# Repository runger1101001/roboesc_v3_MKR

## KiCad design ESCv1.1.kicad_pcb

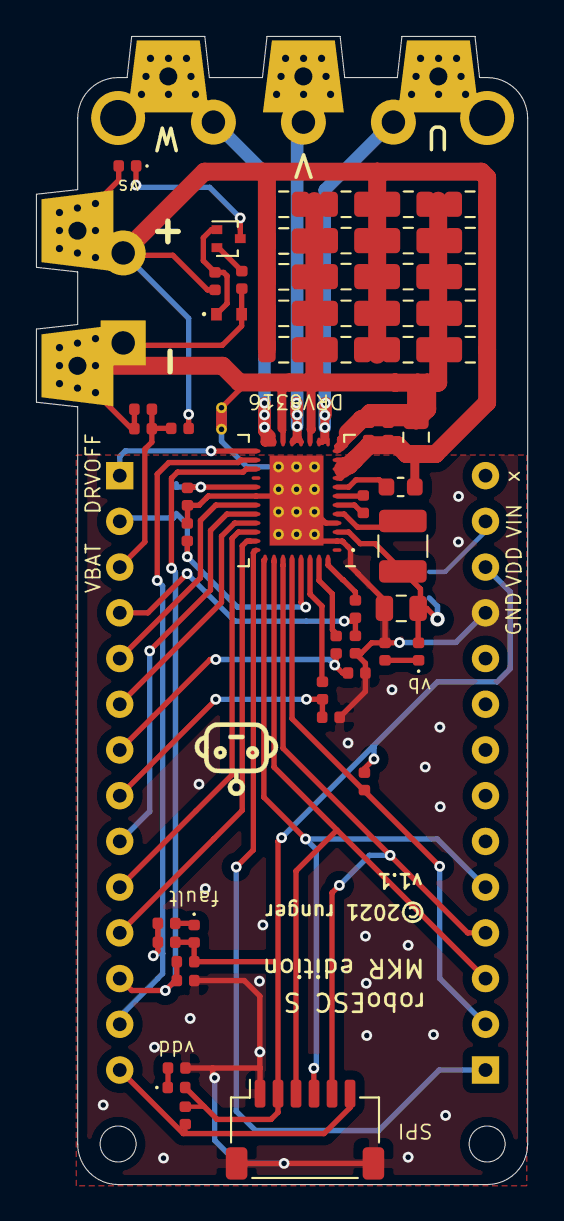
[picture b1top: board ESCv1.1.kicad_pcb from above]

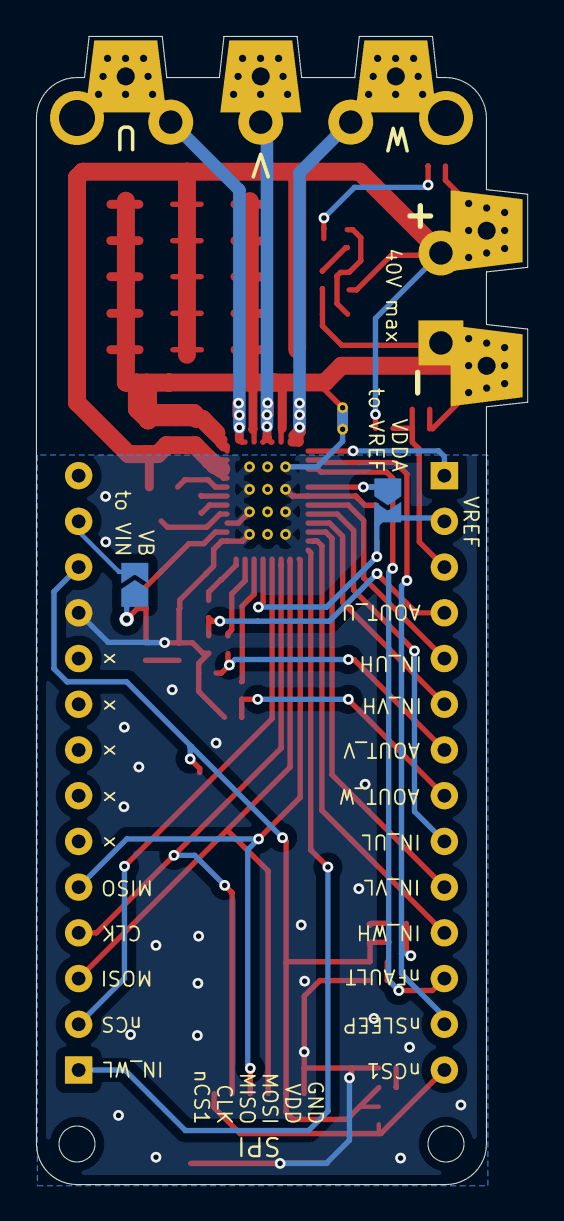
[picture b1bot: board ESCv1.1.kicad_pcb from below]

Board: 2 copper layers, 27.3 x 63.8 mm, 64 parts (3 on the bottom side), 42 nets.

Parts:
C1: 1uF 16V 10%; C_0402_1005Metric
C2: 1nF 16V; C_0402_1005Metric
C3: 22uF 16V; C_0805_2012Metric
C5: 1uF 16V X7R; C_0603_1608Metric
C6: 47nF 50V X7R; C_0402_1005Metric
C7, C8, C9, C11: 100nF 50V 5%; C_0402_1005Metric
C10, C15, C16, C17, C18, C19, C20, C21, C22, C23, C24, C25, C26, C27, C28, C29, C30, C31, C32, C33, C34: 10uF 50V; C_0805_2012Metric
C12, C13, C14: 22pF 50V 1%; C_0402_1005Metric
D1, D2, D3: green; LED_0402_1005Metric
D4: 2.84V; D_SOD-523
D5: red; LED_0402_1005Metric
J1: ST_SH_SM06B-SRSS-TB_1x06-1MP; JST_SH_SM06B-SRSS-TB_1x06-1MP_P1.00mm_Horizontal
J3_1: PWR_Pads; EdgeSolderPads2x_Trapezoidal_3mmx3mmx3mm
J3_2: PWR_IN; TerminalBlock_RND_205-00001_1x02_P5.00mm_Horizontal
J4_1: Phase_Pads; EdgeSolderPads3x_Trapezoidal_3mmx3mmx3mm
J4_2: 1x3 Header; TerminalBlock_RND_205-00277_1x03_P5.00mm_Vertical
JP1, JP5: VSS2VDD; SolderJumper-2_P1.3mm_Open_TrianglePad1.0x1.5mm
L1: 47uH; L_1210_3225Metric
NT1: Net-Tie; NetTie-2_THT_Pad0.3mm
Q1: BC847BTT1G; SOT-416
R1, R6: 1k; R_0402_1005Metric
R2, R3, R8, R14: 5.1k; R_0402_1005Metric
R7: 10k; R_0402_1005Metric
R9: 200Ω; R_0402_1005Metric
R10, R11, R12: 330Ω; R_0402_1005Metric
R13: 100Ω; R_0402_1005Metric
R15: 47k; R_0402_1005Metric
R16: 2.2k; R_0402_1005Metric
U1: DRV8316; vQFN-40_EP_5x7_Pitch0.5mm
U2: ArdunioMKR_Shield; ArduinoMKR_Shield

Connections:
AOUT_U: C14.1, R12.1, U2.4
AOUT_V: C13.1, R11.1, U2.7
AOUT_W: C12.1, R10.1, U2.8
CLK: J1.5, U1.35, U2.25
CP: C5.2, U1.8
CPH: C6.1, U1.7
CPL: C6.2, U1.6
DRVOFF: U1.21, U2.1
FB_BK: C3.1, D3.2, JP1.1, L1.1, U1.3
GND: C1.2, C2.2, C3.2, C11.2, C12.2, C13.2, C14.2, J1.1, J1.MP, NT1.1, R1.1, R6.1, U1.2, U1.4, U1.26, U1.EPAD, U2.18
GNDPWR: C7.2, C8.2, C9.2, C10.2, C15.2, C16.2, C17.2, C18.2, C19.2, C20.2, C21.2, C22.2, C23.2, C24.2, C25.2, C26.2, C27.2, C28.2, C29.2, C30.2, C31.2, C32.2, C33.2, C34.2, D4.2, J3_1.1, J3_2.1, NT1.2, R9.1, R16.1, U1.12, U1.15, U1.18
IN_UH: U1.27, U2.5
IN_UL: U1.28, U2.9
IN_VH: U1.29, U2.6
IN_VL: U1.30, U2.10
IN_WH: U1.31, U2.11
IN_WL: U1.32, U2.28
MISO: J1.4, U1.33, U2.24
MOSI: J1.3, U1.34, U2.26
unnamed: D1.1, R6.2
unnamed: D2.1, Q1.3
unnamed: D3.1, R1.2
unnamed: D4.1, Q1.1, R7.1
unnamed: D5.1, R13.2
unnamed: Q1.2, R9.2
unnamed: R10.2, U1.38
unnamed: R11.2, U1.39
unnamed: R12.2, U1.40
PHASE_U: J4_1.3, J4_2.3, U1.13, U1.14
PHASE_V: J4_1.2, J4_2.2, U1.16, U1.17
PHASE_W: J4_1.1, J4_2.1, U1.19, U1.20
SW_BK: L1.2, U1.5
VBAT: C9.1, R15.1, R16.2, U2.3
VDD: D1.2, D5.2, J1.2, R2.2, R3.1, R8.1, R14.1, U2.17
VDDA: C1.1, JP5.1, U1.25
VIN: JP1.2, U2.16
VREF: C11.1, JP5.2, U1.37, U2.2
VS: C5.1, C7.1, C8.1, C10.1, C15.1, C16.1, C17.1, C18.1, C19.1, C20.1, C21.1, C22.1, C23.1, C24.1, C25.1, C26.1, C27.1, C28.1, C29.1, C30.1, C31.1, C32.1, C33.1, C34.1, D2.2, J3_1.2, J3_2.2, R7.2, R15.2, U1.9, U1.10, U1.11
nCS: R14.2, U1.36, U2.27
nCS1: J1.6, R3.2, U2.14
nFAULT: R8.2, R13.1, U1.22, U2.13
nSLEEP: C2.1, R2.1, U1.23, U2.12

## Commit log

2021-05-07 v1.1 update, fixed pin assignment for nFAULT
2021-05-21 fixed U1 footprint's solder mask

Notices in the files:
ESCv1.1.kicad_pcb:
©2021 runger
